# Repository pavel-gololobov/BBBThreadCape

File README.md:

# BBBThreadCape
BeagleBone Black Cape for OpenThread based on CC2538 module

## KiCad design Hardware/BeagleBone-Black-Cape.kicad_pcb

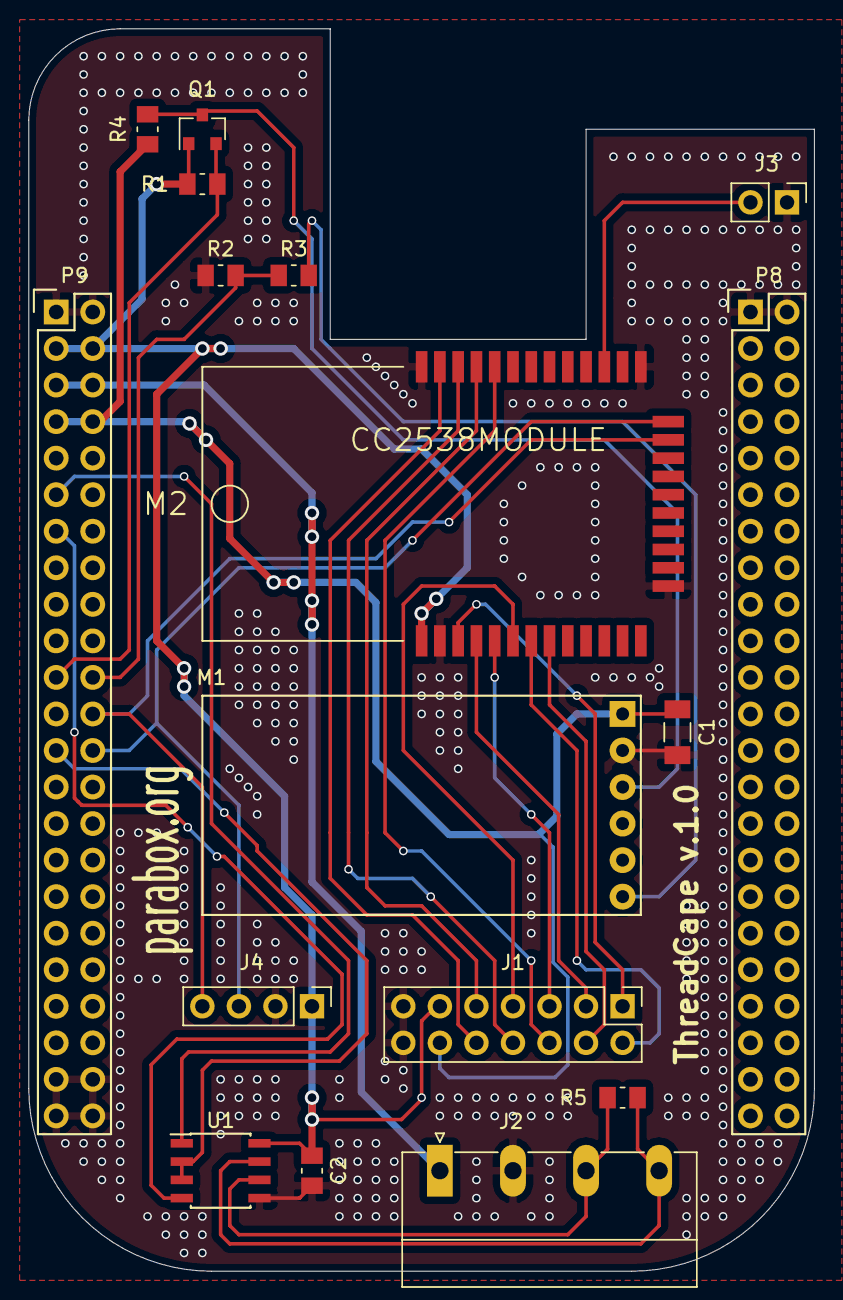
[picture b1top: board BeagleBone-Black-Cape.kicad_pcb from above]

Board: 2 copper layers, 54.6 x 86.4 mm, 17 parts (0 on the bottom side), 26 nets.

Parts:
C1: 10u; C_1206_3216Metric_Pad1.24x1.80mm_HandSolder
C2: 0.1u; C_0805_2012Metric_Pad1.15x1.50mm_HandSolder
J1: MISC; PinHeader_2x07_P2.54mm_Vertical
J2: POWER; PhoenixContact_MC_1,5_4-G-5.08_1x04_P5.08mm_Horizontal
J3: BOOT; PinHeader_1x02_P2.54mm_Vertical
J4: BOOT; PinHeader_1x04_P2.54mm_Vertical
M1: MR1132
M2: CC2538MODULE; CC2538MOD
P8, P9: BeagleBone_Black_Header; Socket_BeagleBone_Black
Q1: 2N7002; SOT-23
R1, R3, R4: 10k; R_0805_2012Metric_Pad1.15x1.50mm_HandSolder
R2: 20k; R_0805_2012Metric_Pad1.15x1.50mm_HandSolder
R5: 120; R_0805_2012Metric_Pad1.15x1.50mm_HandSolder
U1: MAX3072E; SOIC-8_3.9x4.9mm_P1.27mm

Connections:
+3V3: C2.1, J1.11, J4.1, M2.1, P9.3, P9.4, Q1.1, R1.1, U1.8
+5V: J2.1, P9.5, P9.6
/BOOT: J3.2, M2.26
/PB4: J1.4, M2.8
/PB5: J1.2, M2.7
/PD1: J1.6, M2.32
/PD3: J1.8, M2.34
/PD4: J1.10, M2.35
/RESET: J1.9, M2.33
/RS485_A: J2.3, R5.1, U1.6
/RS485_B: J2.4, R5.2, U1.7
/TCK: J1.3, M2.4
/TDI: J1.7, M2.6
/TDO: J1.5, M2.5
/TMS: J1.1, M2.3
/UART0_BOOT_RX: J4.4, M2.22, P9.24
/UART0_BOOT_TX: J4.3, M2.23, P9.26
/UART1_5V_RX: M1.3, Q1.3, R4.2
/UART1_5V_TX: M1.6, R3.2
/UART1_RX: P9.21, Q1.2, R1.2
/UART1_TX: P9.22, R2.2, R3.1
/UART2_RE_DE: P9.25, U1.2, U1.3
/UART2_RX: P9.13, U1.4
/UART2_TX: P9.11, U1.1
GNDD: C1.2, C2.2, J1.13, J1.14, J2.2, J3.1, J4.2, M1.2, M2.2, M2.14, M2.24, M2.36, P8.1, P8.2, P9.1, P9.2, P9.43, P9.44, P9.45, P9.46, R2.1, U1.5
SYS_5V: C1.1, J1.12, M1.1, P9.7, P9.8, R4.1

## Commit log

2018-03-25 complete
2018-03-30 Final version
2018-04-01 Final release 1.0, add gerber files
